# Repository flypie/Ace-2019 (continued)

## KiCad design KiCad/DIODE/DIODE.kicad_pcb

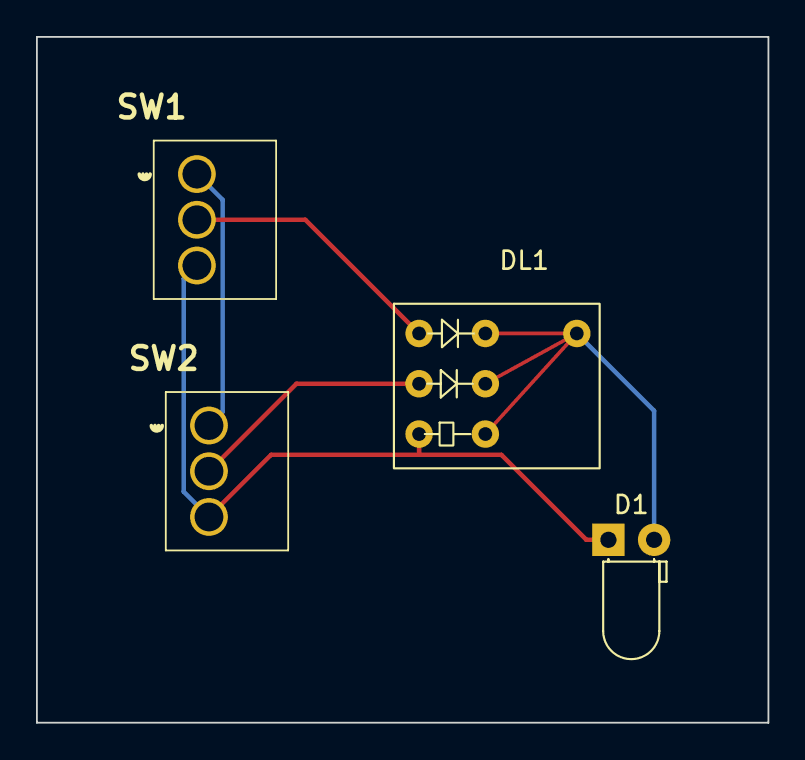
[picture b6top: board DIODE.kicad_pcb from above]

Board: 2 copper layers, 40.6 x 38.1 mm, 4 parts (0 on the bottom side), 5 nets.

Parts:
D1: LED; LED_D3.0mm_Horizontal_O1.27mm_Z2.0mm
DL1: DIODE_OR
SW1, SW2: SW_SPDT; B13AP

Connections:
GND: D1.1 (K), DL1.3 (GND), SW1.3 (C), SW2.3 (C)
unnamed: DL1.1 (A), SW1.2 (B)
unnamed: DL1.2 (B), SW2.2 (B)
unnamed: D1.2 (A), DL1.4 (&)
VCC: SW1.1 (A), SW2.1 (A)

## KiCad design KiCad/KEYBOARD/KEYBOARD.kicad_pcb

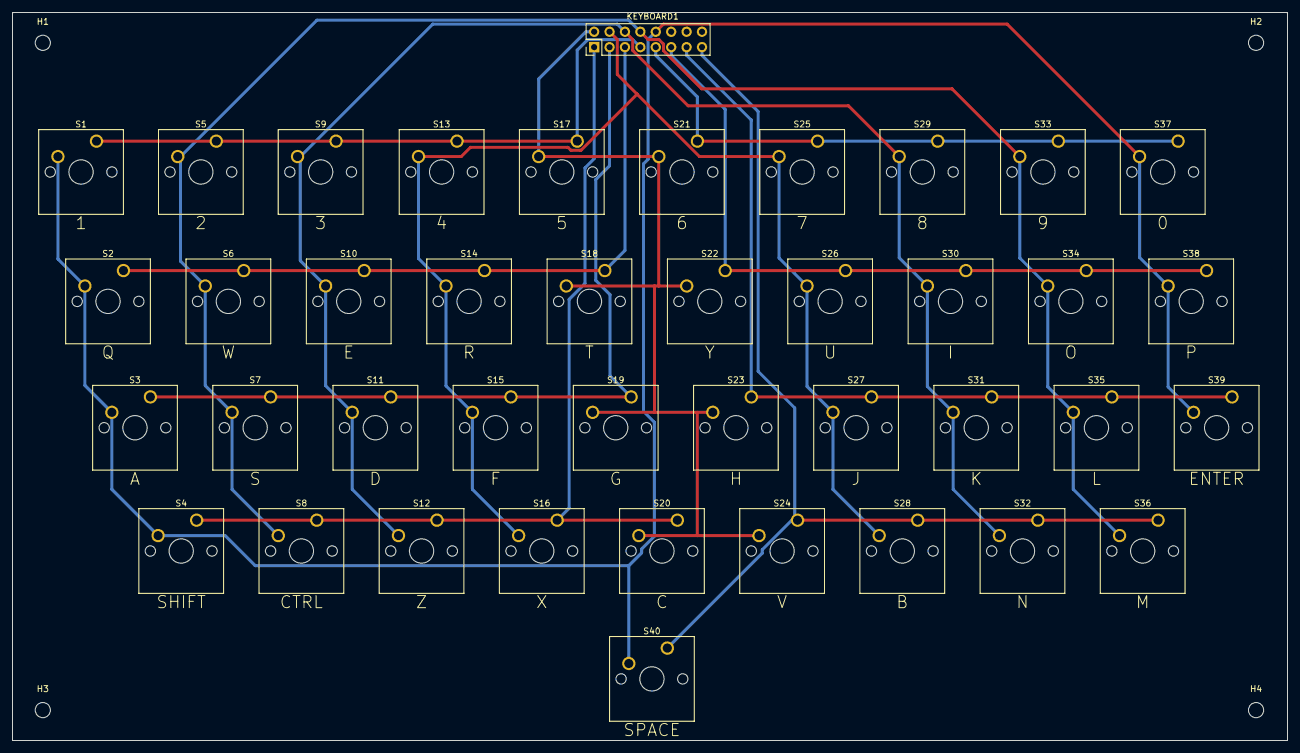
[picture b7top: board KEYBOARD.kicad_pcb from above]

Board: 2 copper layers, 210.2 x 120.0 mm, 45 parts (0 on the bottom side), 13 nets.

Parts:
H1, H2, H3, H4: MountingHole; MountingHole_2.5mm
KEYBOARD1: Conn_02x08_Odd_Even; PinHeader_2x08_P2.54mm_Vertical
S1: 1; SW_Cherry_MX_1.00u_PCB
S2: Q; SW_Cherry_MX_1.00u_PCB
S3: A; SW_Cherry_MX_1.00u_PCB
S4: SHIFT; SW_Cherry_MX_1.00u_PCB
S5: 2; SW_Cherry_MX_1.00u_PCB
S6: W; SW_Cherry_MX_1.00u_PCB
S7: S; SW_Cherry_MX_1.00u_PCB
S8: CTRL; SW_Cherry_MX_1.00u_PCB
S9: 3; SW_Cherry_MX_1.00u_PCB
S10: E; SW_Cherry_MX_1.00u_PCB
S11: D; SW_Cherry_MX_1.00u_PCB
S12: Z; SW_Cherry_MX_1.00u_PCB
S13: 4; SW_Cherry_MX_1.00u_PCB
S14: R; SW_Cherry_MX_1.00u_PCB
S15: F; SW_Cherry_MX_1.00u_PCB
S16: X; SW_Cherry_MX_1.00u_PCB
S17: 5; SW_Cherry_MX_1.00u_PCB
S18: T; SW_Cherry_MX_1.00u_PCB
S19: G; SW_Cherry_MX_1.00u_PCB
S20: C; SW_Cherry_MX_1.00u_PCB
S21: 6; SW_Cherry_MX_1.00u_PCB
S22: Y; SW_Cherry_MX_1.00u_PCB
S23: H; SW_Cherry_MX_1.00u_PCB
S24: V; SW_Cherry_MX_1.00u_PCB
S25: 7; SW_Cherry_MX_1.00u_PCB
S26: U; SW_Cherry_MX_1.00u_PCB
S27: J; SW_Cherry_MX_1.00u_PCB
S28: B; SW_Cherry_MX_1.00u_PCB
S29: 8; SW_Cherry_MX_1.00u_PCB
S30: I; SW_Cherry_MX_1.00u_PCB
S31: K; SW_Cherry_MX_1.00u_PCB
S32: N; SW_Cherry_MX_1.00u_PCB
S33: 9; SW_Cherry_MX_1.00u_PCB
S34: O; SW_Cherry_MX_1.00u_PCB
S35: L; SW_Cherry_MX_1.00u_PCB
S36: M; SW_Cherry_MX_1.00u_PCB
S37: 0; SW_Cherry_MX_1.00u_PCB
S38: P; SW_Cherry_MX_1.00u_PCB
S39: ENTER; SW_Cherry_MX_1.00u_PCB
S40: SPACE; SW_Cherry_MX_1.00u_PCB

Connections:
/A8: KEYBOARD1.1, S4.1, S8.1, S12.1, S16.1, S20.1
/A9: KEYBOARD1.3, S3.1, S7.1, S11.1, S15.1, S19.1
/A10: KEYBOARD1.5, S2.1, S6.1, S10.1, S14.1, S18.1
/A11: KEYBOARD1.7, S1.1, S5.1, S9.1, S13.1, S17.1
/A12: KEYBOARD1.9, S21.1, S25.1, S29.1, S33.1, S37.1
/A13: KEYBOARD1.11, S22.1, S26.1, S30.1, S34.1, S38.1
/A14: KEYBOARD1.13, S23.1, S27.1, S31.1, S35.1, S39.1
/A15: KEYBOARD1.15, S24.1, S28.1, S32.1, S36.1, S40.1
unnamed: KEYBOARD1.2, S17.2, S18.2, S19.2, S20.2, S21.2, S22.2, S23.2, S24.2
unnamed: KEYBOARD1.4, S13.2, S14.2, S15.2, S16.2, S25.2, S26.2, S27.2, S28.2
unnamed: KEYBOARD1.6, S9.2, S10.2, S11.2, S12.2, S29.2, S30.2, S31.2, S32.2
unnamed: KEYBOARD1.8, S5.2, S6.2, S7.2, S8.2, S33.2, S34.2, S35.2, S36.2
unnamed: KEYBOARD1.10, S1.2, S2.2, S3.2, S4.2, S37.2, S38.2, S39.2, S40.2

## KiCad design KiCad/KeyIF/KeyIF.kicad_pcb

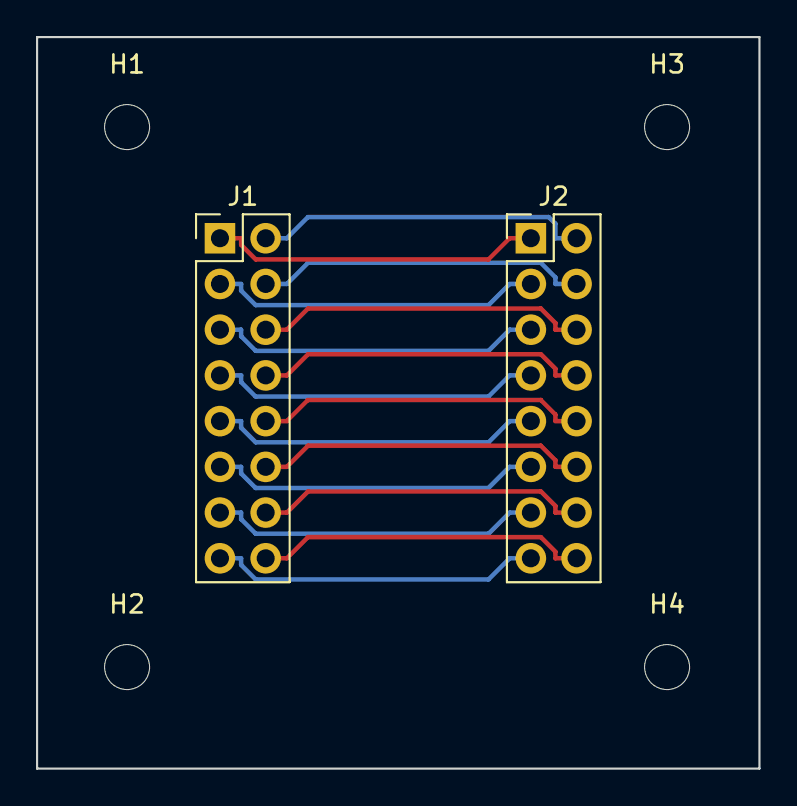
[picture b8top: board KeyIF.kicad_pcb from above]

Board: 2 copper layers, 40.1 x 40.6 mm, 6 parts (0 on the bottom side), 16 nets.

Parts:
H1, H2, H3, H4: MountingHole; MountingHole_2.5mm
J1, J2: Conn_02x08_Odd_Even; PinHeader_2x08_P2.54mm_Vertical

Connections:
unnamed: J1.1, J2.1
unnamed: J1.2, J2.2
unnamed: J1.3, J2.3
unnamed: J1.4, J2.4
unnamed: J1.5, J2.5
unnamed: J1.6, J2.6
unnamed: J1.7, J2.7
unnamed: J1.8, J2.8
unnamed: J1.9, J2.9
unnamed: J1.10, J2.10
unnamed: J1.11, J2.11
unnamed: J1.12, J2.12
unnamed: J1.13, J2.13
unnamed: J1.14, J2.14
unnamed: J1.15, J2.15
unnamed: J1.16, J2.16
